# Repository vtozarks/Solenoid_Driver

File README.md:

# 2 Channel Opto Isolated FET Solenoid Driver
KiCAD 7.0 design files
LTSpice schematic
Associated data sheets

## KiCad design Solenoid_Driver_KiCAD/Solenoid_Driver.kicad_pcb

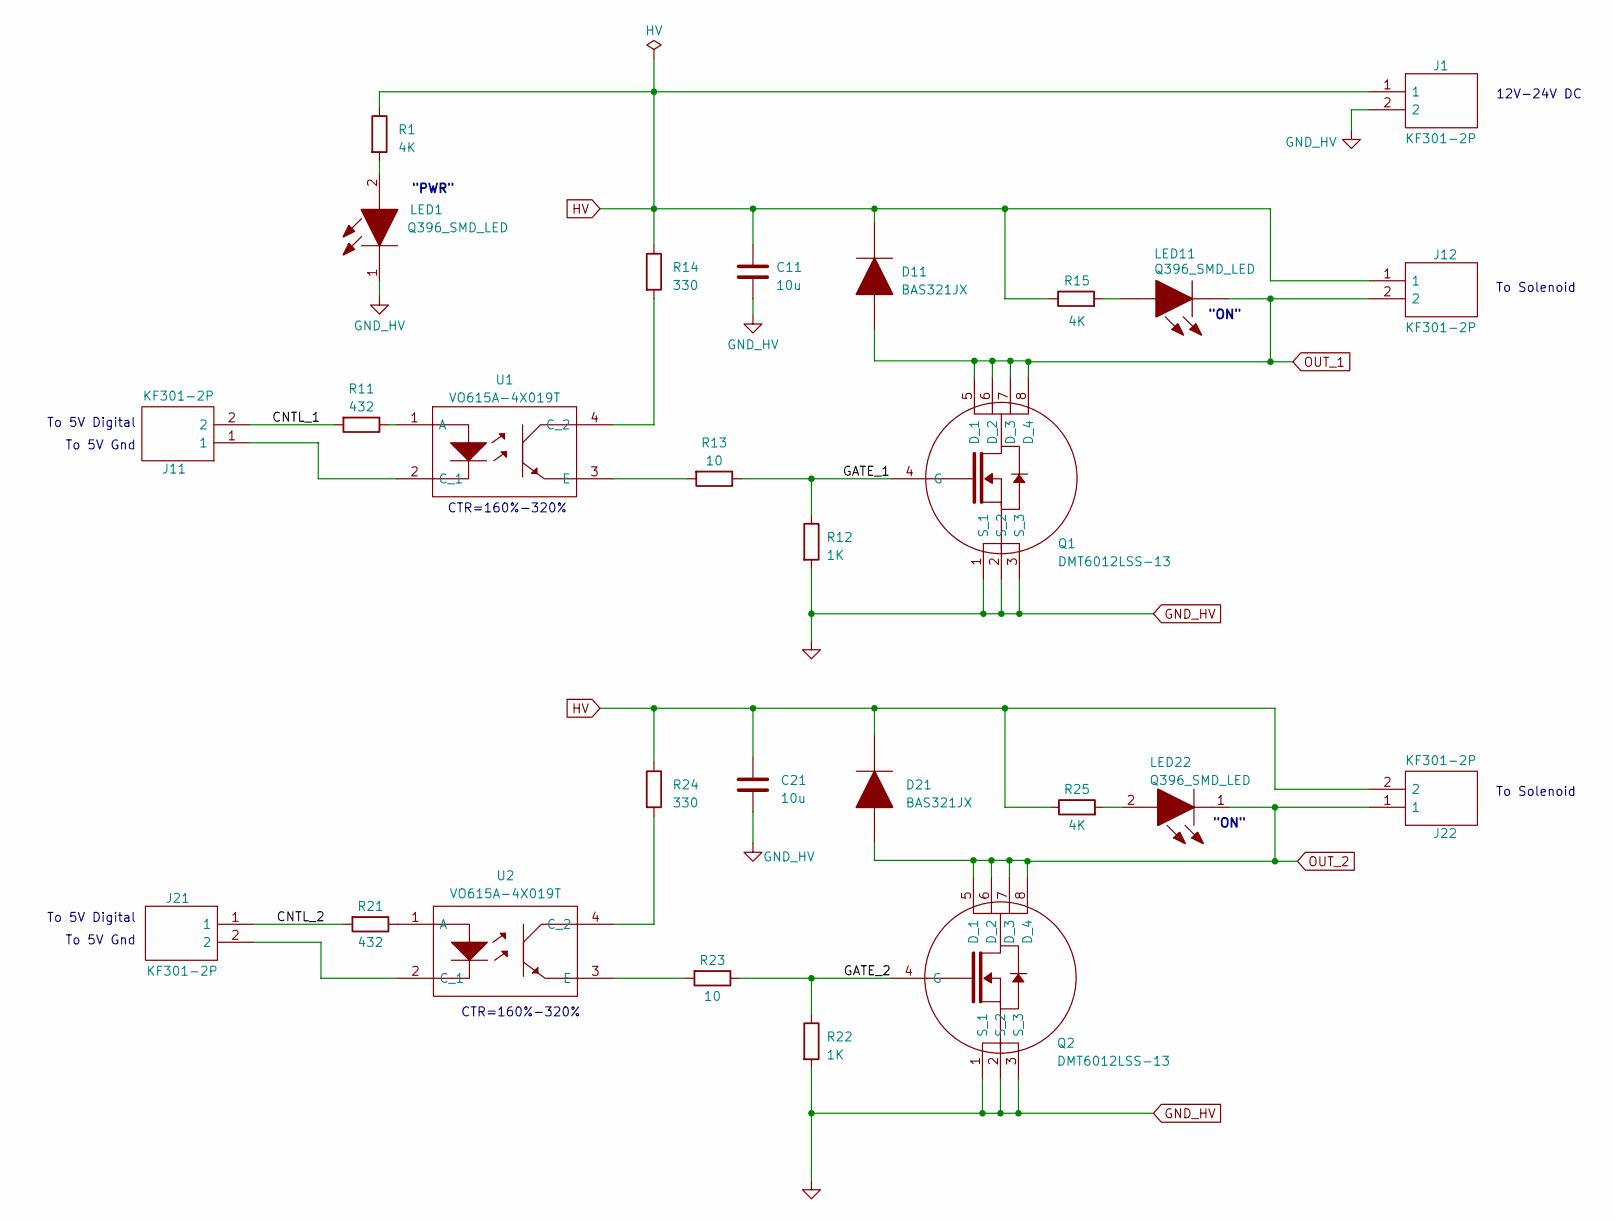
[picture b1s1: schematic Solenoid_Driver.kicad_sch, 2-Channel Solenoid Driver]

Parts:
C11, C21: 10u; C_1206_3216Metric_Pad1.33x1.80mm_HandSolder
D11, D21: BAS321JX; SODFL2512X80N; Manufacturer_Part_Number BAS321JX; Mouser Part Number 771-BAS321JX
J1, J11, J12, J21, J22: KF301-2P; KF3012P; Manufacturer_Part_Number KF301-2P
LED1, LED11, LED22: Q396_SMD_LED; LEDC1608X80N; Manufacturer_Part_Number Q396-P1Q2-36; Mouser Part Number 720-LYQ396P1Q236
Q1, Q2: DMT6012LSS-13; SOIC127P600X150-8N; Manufacturer_Part_Number DMT6012LSS-13; Mouser Part Number 621-DMT6012LSS-13
R1, R15, R25: 4K; R_0603_1608Metric_Pad0.98x0.95mm_HandSolder
R11, R21: 432; R_0603_1608Metric_Pad0.98x0.95mm_HandSolder
R12, R22: 1K; R_0603_1608Metric_Pad0.98x0.95mm_HandSolder
R13, R23: 10; R_0603_1608Metric_Pad0.98x0.95mm_HandSolder
R14, R24: 330; R_0603_1608Metric_Pad0.98x0.95mm_HandSolder
U1, U2: VO615A-4X019T; SMD-4-OPT9_VO615A_VIS-M; Manufacturer_Part_Number VO615A; Mouser Part Number 78-VO615A

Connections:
/CNTL_1: J11.2, R11.2
/CNTL_2: J21.1, R21.2
/GATE_1: Q1.4 (G), R12.1, R13.1
/GATE_2: Q2.4 (G), R22.1, R23.1
GND_HV: C11.2, C21.2, J1.2, LED1.1, Q1.1 (S_1), Q1.2 (S_2), Q1.3 (S_3), Q2.1 (S_1), Q2.2 (S_2), Q2.3 (S_3), R12.2, R22.2
HV: C11.1, C21.1, D11.1, D21.1, J1.1, J12.1, J22.2, R1.1, R14.1, R15.1, R24.1, R25.1
unnamed: LED1.2, R1.2
unnamed: LED11.2, R15.2
unnamed: LED22.2, R25.2
unnamed: R11.1, U1.1 (A)
unnamed: J11.1, U1.2 (C_1)
unnamed: R14.2, U1.4 (C_2)
unnamed: R13.2, U1.3 (E)
unnamed: R21.1, U2.1 (A)
unnamed: J21.2, U2.2 (C_1)
unnamed: R24.2, U2.4 (C_2)
unnamed: R23.2, U2.3 (E)
OUT_1: D11.2, J12.2, LED11.1, Q1.5 (D_1), Q1.6 (D_2), Q1.7 (D_3), Q1.8 (D_4)
OUT_2: D21.2, J22.1, LED22.1, Q2.5 (D_1), Q2.6 (D_2), Q2.7 (D_3), Q2.8 (D_4)

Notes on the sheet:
"ON"
CTR=160%-320%
To Solenoid
To 5V Gnd
To 5V Digital
12V-24V DC
"PWR"

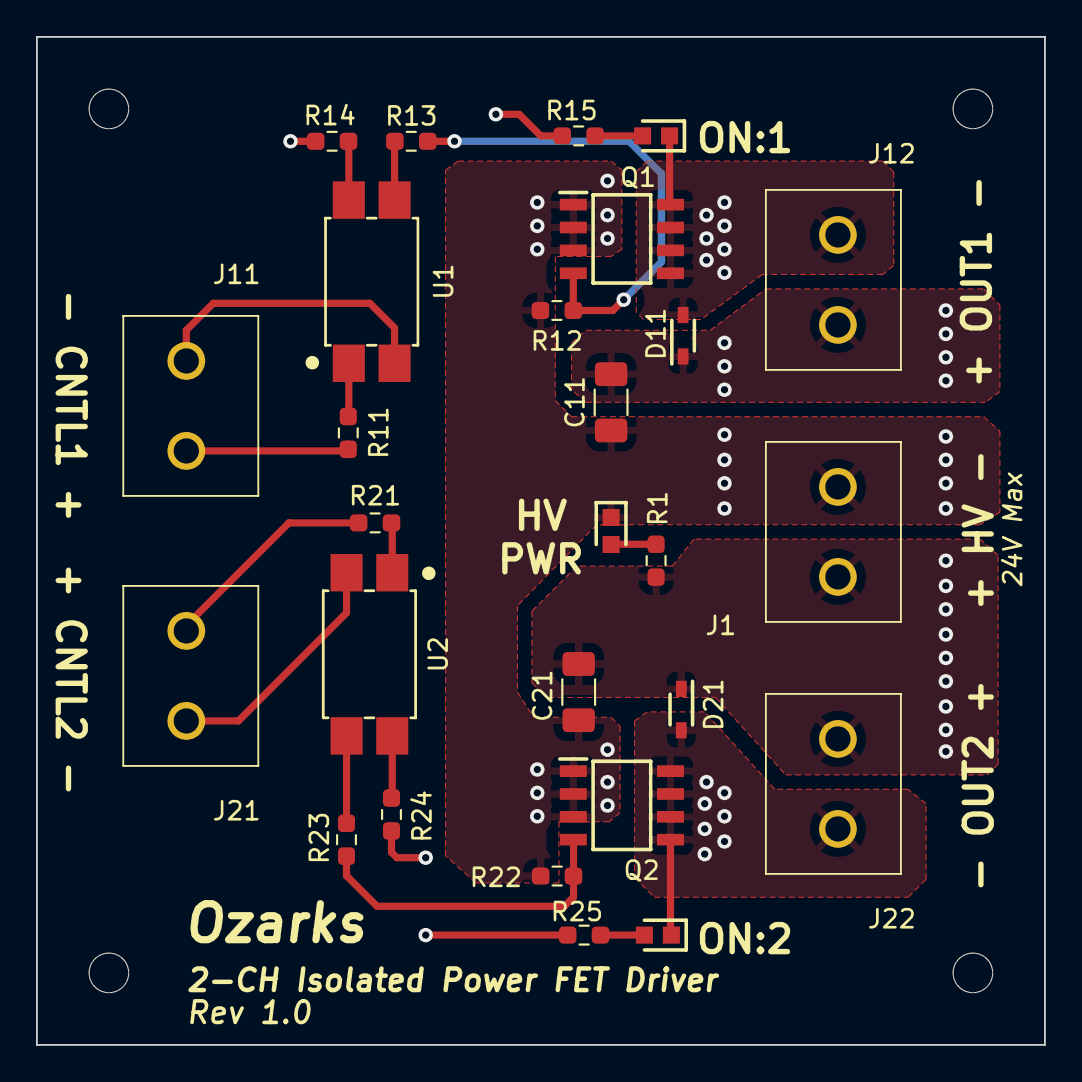
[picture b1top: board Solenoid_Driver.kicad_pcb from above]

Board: 4 copper layers, 56.0 x 56.0 mm, 27 parts (0 on the bottom side), 19 nets.

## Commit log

2023-05-27 Iniital check-in
2023-05-27 Adding KiCad files and Gerbers
